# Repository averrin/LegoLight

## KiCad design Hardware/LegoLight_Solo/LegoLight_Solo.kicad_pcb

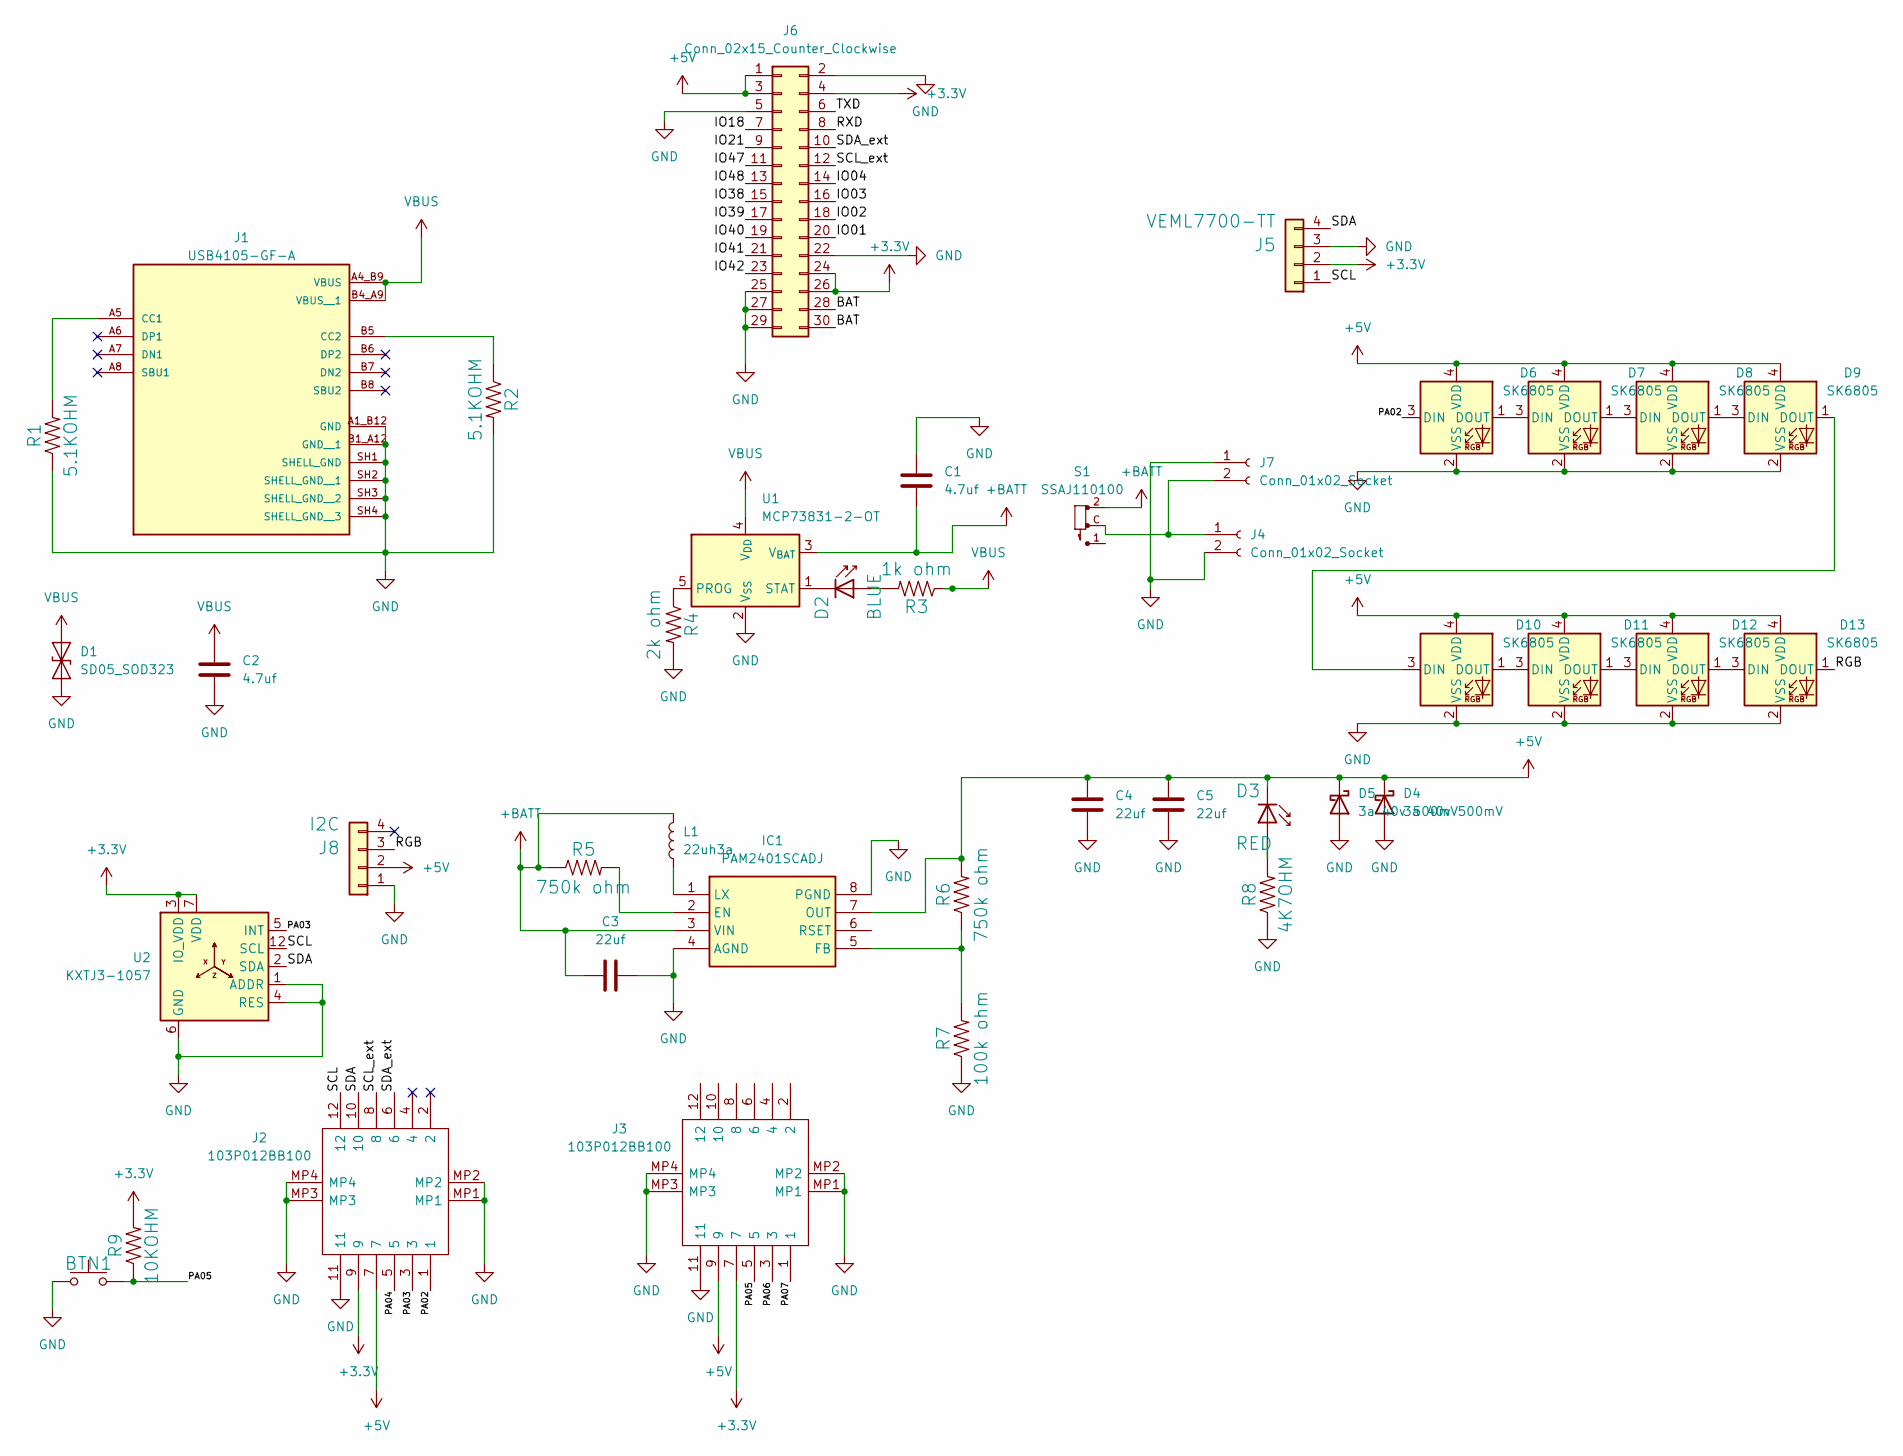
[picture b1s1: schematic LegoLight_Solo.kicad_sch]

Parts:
BTN1: BTN; B3U-1000P; PARTREV C; Mouser Part Number 653-B3U-1000P
C1, C2: 4.7uf; C_0805_2012Metric; Mouser Part Number 80-C0805C475K4RAUTO
C3, C4, C5: 22uf; C_0805_2012Metric; Mouser Part Number 80-C0805C226M9P
D1: SD05_SOD323; D_SOD-323; Mouser Part Number 771-PESD5V0V1771-BA
D2: BLUE; LED_0805_2012Metric_Pad1.15x1.40mm_HandSolder; Mouser Part Number 710-150080BS75000
D3: RED; LED_0805_2012Metric_Pad1.15x1.40mm_HandSolder; Mouser Part Number 696-SML-LXT0805IW
D4, D5: 3a 40v 500mV; D_2010_5025Metric; Mouser Part Number 621-B340A-F
D6, D7, D8, D9, D10, D11, D12, D13: SK6805; LED_SK6812_EC15_1.5x1.5mm; Mouser Part Number 485-4492
IC1: PAM2401SCADJ; SOP65P490X110-8N; Mouser Part Number 621-PAM2401SCADJ
J1: USB4105-GF-A; GCT_USB4105-GF-A; PARTREV B3; Mouser Part Number 640-USB4105-GF-A
J2, J3: 103P012BB100; 103R012BB100; Mouser Part Number 649-103P012BB100
J4: Conn_01x02_Socket; JST_PH_S2B-PH-SM4-TB_1x02-1MP_P2.00mm_Horizontal; Mouser Part Number 485-1769
J5: VEML7700-TT; XDCR_VEML7700-TT; Mouser Part Number 78-VEML7700-TT
J6: Conn_02x15_Counter_Clockwise; PinSocket_2x15_P1.27mm_Vertical; Mouser Part Number M50-3001545
J7: Conn_01x02_Socket; PinHeader_1x02_P2.54mm_Vertical
J8: I2C; SPARKFUN_PRT-14417; Mouser Part Number 474-PRT-14417
L1: 22uh3a; L_Taiyo-Yuden_MD-5050; Mouser Part Number 652-SRP5050FA-220M1
R1, R2: 5.1KOHM; R_0805_2012Metric_Pad1.20x1.40mm_HandSolder; Mouser Part Number 603-RC0805JR-135K1L
R3: 1k ohm; R_0805_2012Metric_Pad1.20x1.40mm_HandSolder; Mouser Part Number CR0805-FX-1601ELF
R4: 2k ohm; R_0805_2012Metric_Pad1.20x1.40mm_HandSolder; Mouser Part Number CR0805-JW-202ELF
R5, R6: 750k ohm; R_0805_2012Metric_Pad1.20x1.40mm_HandSolder; Mouser Part Number 754-RG2012P-754-B-T5
R7: 100k ohm; R_0805_2012Metric_Pad1.20x1.40mm_HandSolder; Mouser Part Number 754-RG2012P-104-B-T5
R8: 4K7OHM; R_0805_2012Metric_Pad1.20x1.40mm_HandSolder; Mouser Part Number 708-RMCF0805FT4K70
R9: 10KOHM; R_0805_2012Metric_Pad1.20x1.40mm_HandSolder; Mouser Part Number 652-CR0805-JW-103ELF
S1: SSAJ110100; SW_SSAJ110100; PARTREV N/A; Mouser Part Number 688-SSAJ110100
U1: MCP73831-2-OT; SOT-23-5; Mouser Part Number 579-MCP73831T-2ACIOT
U2: KXTJ3-1057; KIONIX_KXTJ3-1057; Mouser Part Number 912-KXTJ3-1057

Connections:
+3.3V: J2.9, J3.7, J5.2, J6.4, J6.24, J6.26, R9.2, U2.3 (IO_VDD), U2.7 (VDD), U2.10 (VDD), U2.11 (IO_VDD)
+5V: C4.2, C5.2, D3.1 (K), D4.1 (K), D5.1 (K), D6.4 (VDD), D7.4 (VDD), D8.4 (VDD), D9.4 (VDD), D10.4 (VDD), D11.4 (VDD), D12.4 (VDD), D13.4 (VDD), IC1.7 (OUT), J2.7, J3.9, J6.1, J6.3, J8.2, R6.2
+BATT: C1.2, C3.1, IC1.3 (VIN), L1.2, R5.1, S1.2, U1.3 (V_{BAT})
/BAT: J6.28, J6.30
/IO01: J6.20
/IO02: J6.18
/IO03: J6.16
/IO04: J6.14
/IO18: J6.7
/IO21: J6.9
/IO38: J6.15
/IO39: J6.17
/IO40: J6.19
/IO41: J6.21
/IO42: J6.23
/IO47: J6.11
/IO48: J6.13
/PA02: D6.3 (DIN), J2.1
/PA03: J2.3, U2.5 (INT)
/PA04: J2.5
/PA05: BTN1.2, J3.5, R9.1
/PA06: J3.3
/PA07: J3.1
/RGB: D13.1 (DOUT), J8.3
/RXD: J6.8
/SCL: J2.12, J5.1, U2.12 (SCL)
/SCL_ext: J2.8, J6.12
/SDA: J2.10, J5.4, U2.2 (SDA)
/SDA_ext: J2.6, J6.10
/TXD: J6.6
GND: BTN1.1, C1.1, C2.2, C3.2, C4.1, C5.1, D1.1 (A1), D4.2 (A), D5.2 (A), D6.2 (VSS), D7.2 (VSS), D8.2 (VSS), D9.2 (VSS), D10.2 (VSS), D11.2 (VSS), D12.2 (VSS), D13.2 (VSS), IC1.4 (AGND), IC1.8 (PGND), J1.A1_B12 (GND), J1.B1_A12 (GND__1), J1.SH1 (SHELL_GND), J1.SH2 (SHELL_GND__1), J1.SH3 (SHELL_GND__2), J1.SH4 (SHELL_GND__3), J2.11, J2.MP1, J2.MP2, J2.MP3, J2.MP4, J3.11, J3.MP1, J3.MP2, J3.MP3, J3.MP4, J4.2, J5.3, J6.2, J6.5, J6.22, J6.25, J6.27, J6.29, J7.1, J8.1, R1.1, R2.2, R4.2, R7.1, R8.1, U1.2 (V_{SS}), U2.1 (ADDR), U2.4 (RES), U2.6 (GND), U2.8 (GND), U2.9 (GND)
unnamed: D2.2 (A), R3.2
unnamed: D2.1 (K), U1.1 (STAT)
unnamed: D3.2 (A), R8.2
unnamed: D6.1 (DOUT), D7.3 (DIN)
unnamed: D7.1 (DOUT), D8.3 (DIN)
unnamed: D8.1 (DOUT), D9.3 (DIN)
unnamed: D9.1 (DOUT), D10.3 (DIN)
unnamed: D10.1 (DOUT), D11.3 (DIN)
unnamed: D11.1 (DOUT), D12.3 (DIN)
unnamed: D12.1 (DOUT), D13.3 (DIN)
unnamed: IC1.2 (EN), R5.2
unnamed: IC1.5 (FB), R6.1, R7.2
unnamed: IC1.1 (LX), L1.1
unnamed: J1.A5 (CC1), R1.2
unnamed: J1.B5 (CC2), R2.1
unnamed: J4.1, J7.2, S1.C
unnamed: R4.1, U1.5 (PROG)
VBUS: C2.1, D1.2 (A2), J1.A4_B9 (VBUS), J1.B4_A9 (VBUS__1), R3.1, U1.4 (V_{DD})

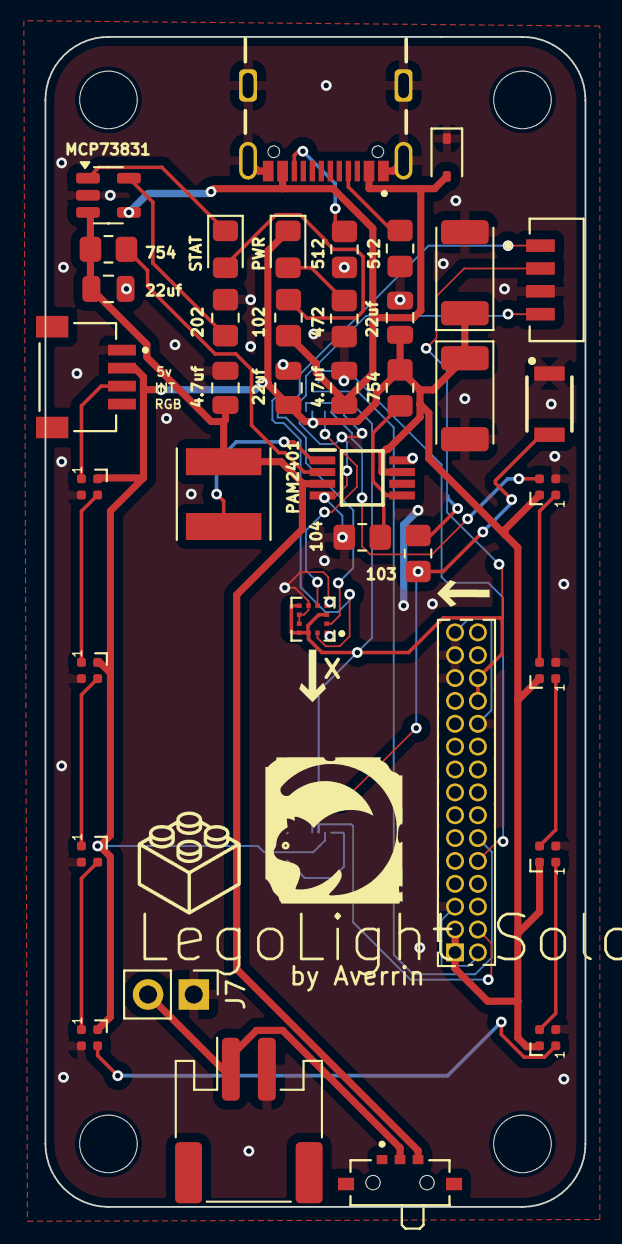
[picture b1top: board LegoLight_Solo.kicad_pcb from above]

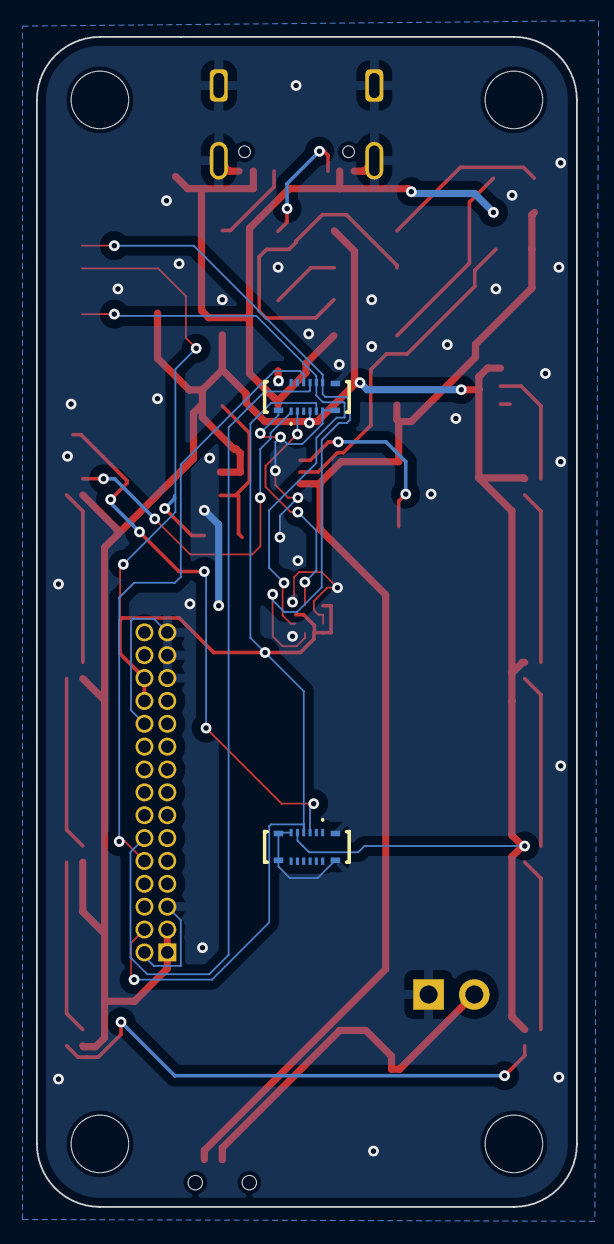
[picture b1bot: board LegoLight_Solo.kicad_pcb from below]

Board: 2 copper layers, 30.0 x 65.0 mm, 45 parts (2 on the bottom side), 31 nets.

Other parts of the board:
H1, H2, H3, H4: MountingHole; MountingHole_3.2mm_M3_DIN965

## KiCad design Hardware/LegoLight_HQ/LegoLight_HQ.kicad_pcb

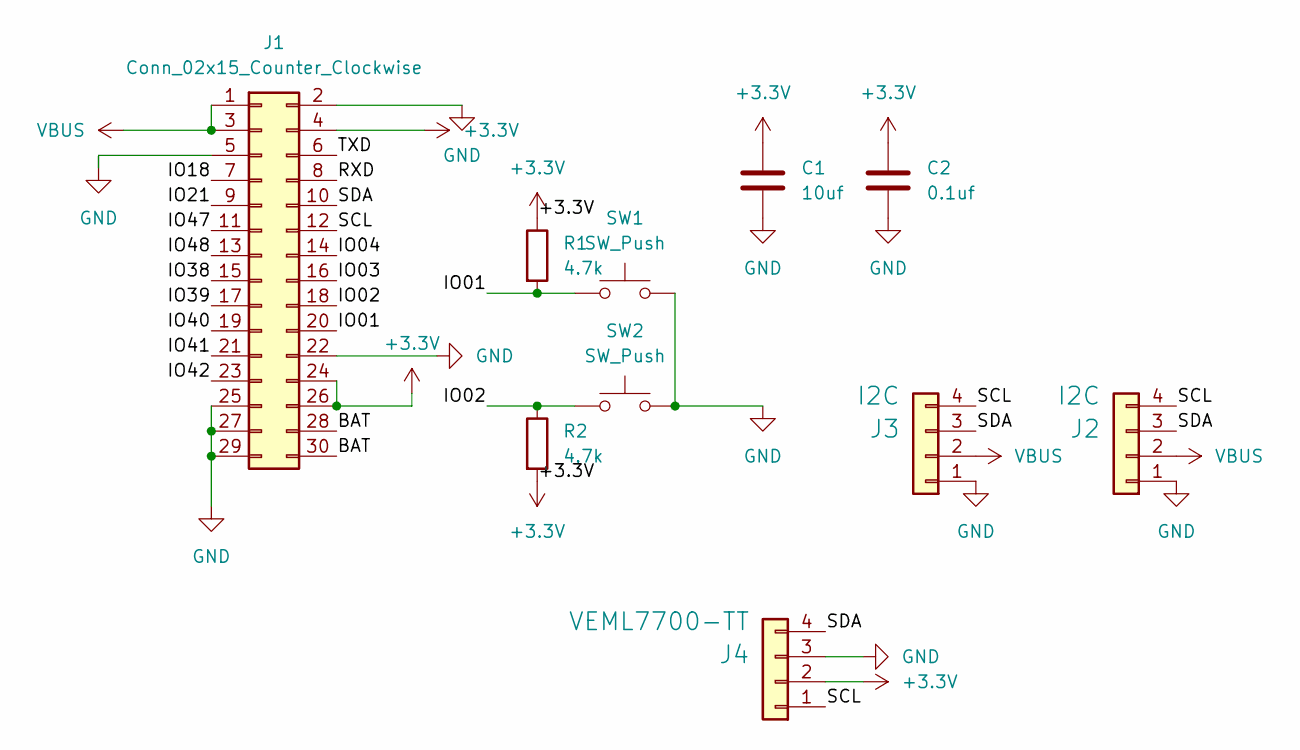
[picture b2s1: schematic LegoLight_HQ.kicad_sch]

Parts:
C1: 10uf; C_0805_2012Metric; Mouser Part Number 80-C0805C106K8R
C2: 0.1uf; C_0805_2012Metric; Mouser Part Number 581-08055C104M4T4A
J1: Conn_02x15_Counter_Clockwise; PinHeader_2x15_P1.27mm_Vertical; Mouser Part Number M50-3001545
J2, J3: I2C; SPARKFUN_PRT-14417; Mouser Part Number 485-4328
J4: VEML7700-TT; XDCR_VEML7700-TT; Mouser Part Number 78-VEML7700-TT
R1, R2: 4.7k; R_1206_3216Metric; Mouser Part Number CR1206-FX-4701ELF
SW1, SW2: SW_Push; SW_MX

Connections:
+3.3V: C1.1, C2.1, J1.4, J1.24, J1.26, J4.2, R1.1, R2.2
/BAT: J1.28, J1.30
/IO01: J1.20, R1.2, SW1.1
/IO02: J1.18, R2.1, SW2.1
/IO03: J1.16
/IO04: J1.14
/IO18: J1.7
/IO21: J1.9
/IO38: J1.15
/IO39: J1.17
/IO40: J1.19
/IO41: J1.21
/IO42: J1.23
/IO47: J1.11
/IO48: J1.13
/RXD: J1.8
/SCL: J1.12, J2.4, J3.4, J4.1
/SDA: J1.10, J2.3, J3.3, J4.4
/TXD: J1.6
GND: C1.2, C2.2, J1.2, J1.5, J1.22, J1.25, J1.27, J1.29, J2.1, J3.1, J4.3, SW1.2, SW2.2
VBUS: J1.1, J1.3, J2.2, J3.2

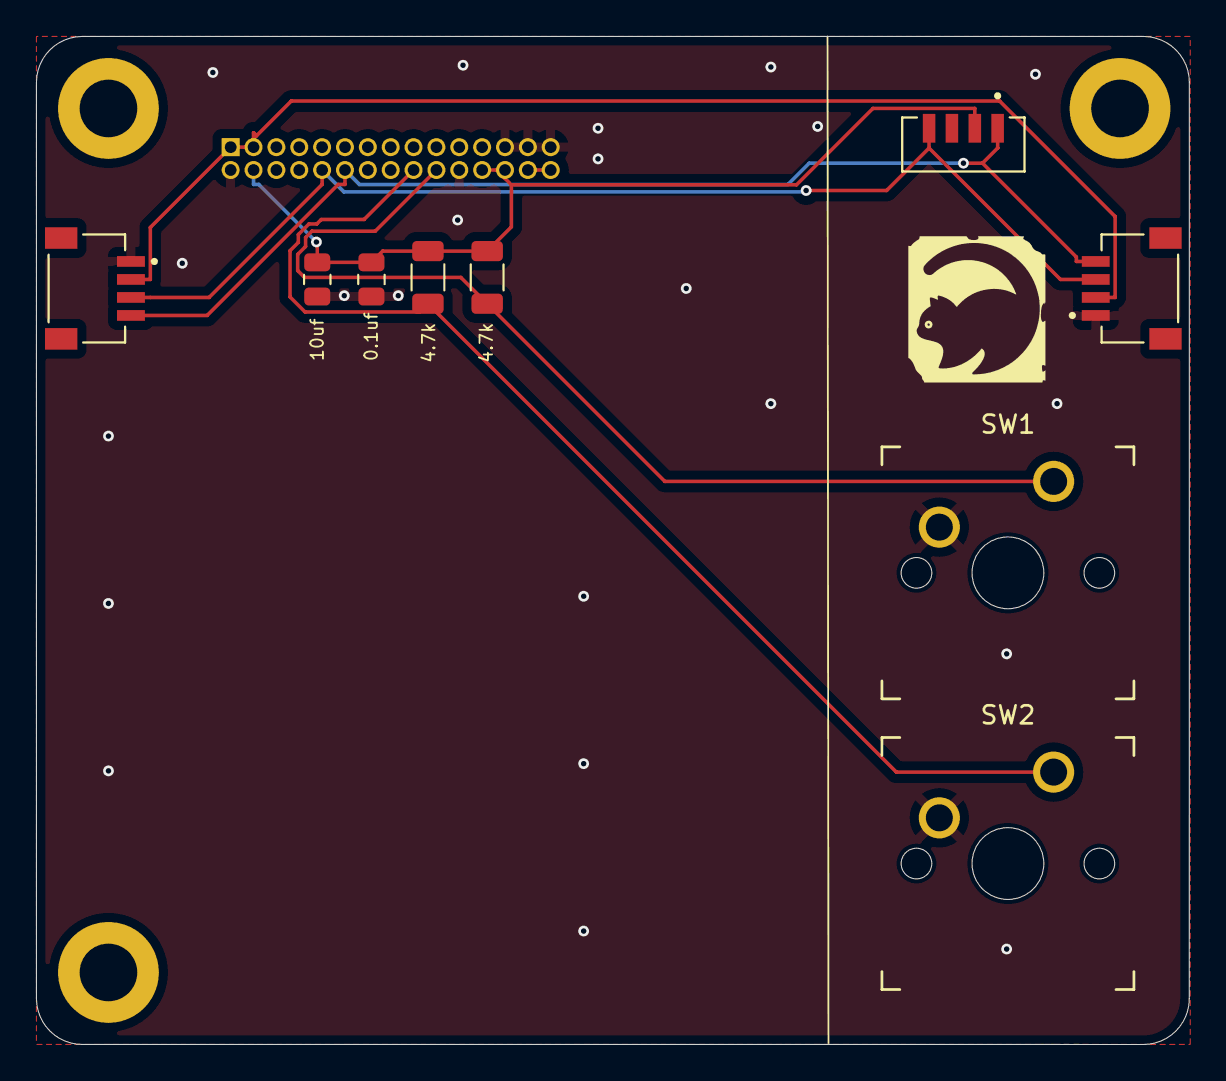
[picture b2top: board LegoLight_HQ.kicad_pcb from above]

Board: 2 copper layers, 64.1 x 56.0 mm, 13 parts (1 on the bottom side), 8 nets.

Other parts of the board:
REF1, REF2, REF3: MountingHole_3.2mm_M3_DIN965_Pad

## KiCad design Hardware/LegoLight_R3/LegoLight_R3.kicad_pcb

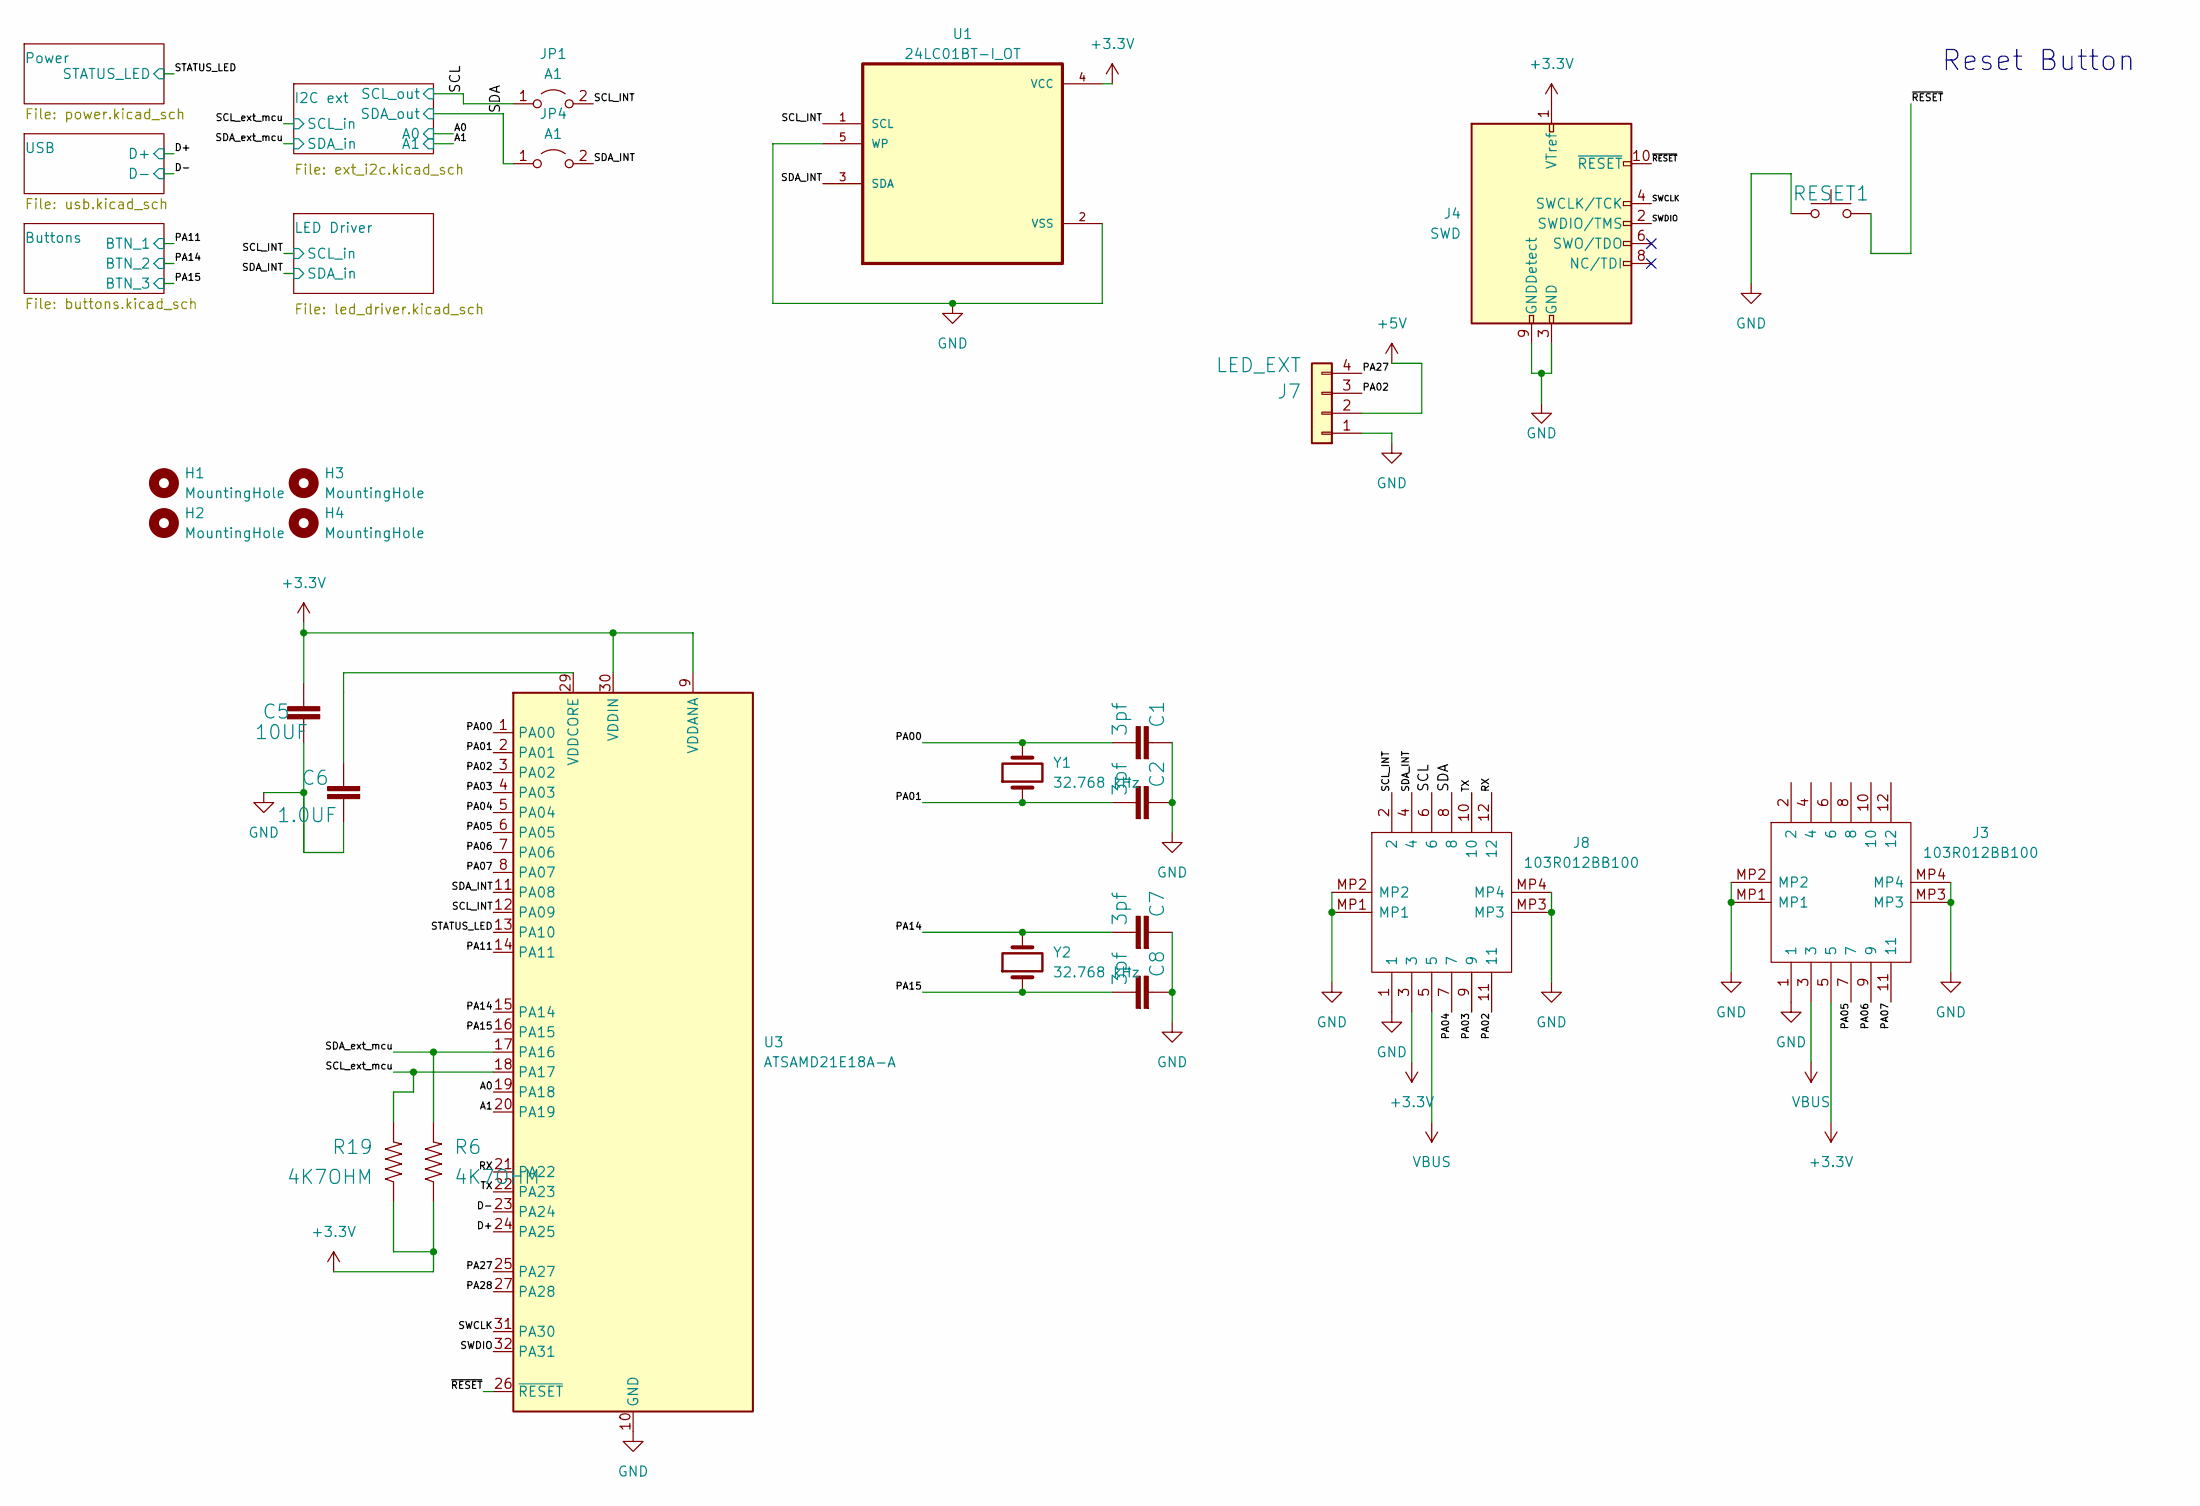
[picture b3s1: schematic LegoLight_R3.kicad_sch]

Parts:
C1, C2, C7, C8: 3pf; C_0805_2012Metric; Mouser Part Number 187-CL21B105KAFNNNE
C5: 10UF; C_0805_2012Metric_Pad1.18x1.45mm_HandSolder; Mouser Part Number 187-CL21A106KOQNNNG
C6: 1.0UF; C_0805_2012Metric_Pad1.18x1.45mm_HandSolder; Mouser Part Number 187-CL21B105KAFNNNE
H1, H2, H3, H4: MountingHole; MountingHole_3.2mm_M3_DIN965
J3, J8: 103R012BB100; Mouser Part Number 649-103R012BB100
J4: SWD; PinSocket_2x05_P1.27mm_Vertical
J7: LED_EXT; SPARKFUN_PRT-14417; Mouser Part Number 485-4328
JP1, JP4: A1; SolderJumper-2_P1.3mm_Open_RoundedPad1.0x1.5mm
R6, R19: 4K7OHM; R_0805_2012Metric_Pad1.20x1.40mm_HandSolder; Mouser Part Number 708-RMCF0805FT4K70
RESET1: TL3305AF160QG; B3U-1000P; PARTREV C; Mouser Part Number 653-B3U-1000P
U1: 24LC01BT-I_OT; SOT-353_SC-70-5; Mouser Part Number 579-24LC01BT-I/OT
U3: ATSAMD21E18A-A; QFN-32-1EP_5x5mm_P0.5mm_EP3.3x3.3mm; Mouser Part Number 556-ATSAMD21E18A-MUT
Y1, Y2: 32.768 kHz; Crystal_SMD_MicroCrystal_CC8V-T1A-2Pin_2.0x1.2mm; Mouser Part Number 815-ABS06-32.768K-T

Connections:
+3.3V: C5.1, J3.5, J4.1 (VTref), J8.3, R6.1, R19.1, U1.4 (VCC), U3.9 (VDDANA), U3.30 (VDDIN); also elsewhere on the board
+5V: J7.2; also elsewhere on the board
/A0: U3.19 (PA18); also elsewhere on the board
/A1: U3.20 (PA19); also elsewhere on the board
/D+: U3.24 (PA25); also elsewhere on the board
/D-: U3.23 (PA24); also elsewhere on the board
/PA00: C1.1, U3.1 (PA00), Y1.2
/PA01: C2.1, U3.2 (PA01), Y1.1
/PA02: J7.3, J8.11, U3.3 (PA02)
/PA03: J8.9, U3.4 (PA03)
/PA04: J8.7, U3.5 (PA04)
/PA05: J3.7, U3.6 (PA05)
/PA06: J3.9, U3.7 (PA06)
/PA07: J3.11, U3.8 (PA07)
/PA11: U3.14 (PA11); also elsewhere on the board
/PA14: C7.1, U3.15 (PA14), Y2.2
/PA15: C8.1, U3.16 (PA15), Y2.1
/PA27: J7.4, U3.25 (PA27)
/PA28: U3.27 (PA28)
/RX: J8.12, U3.21 (PA22)
/SCL: J8.6, JP1.1 (A); also elsewhere on the board
/SCL_INT: J8.2, JP1.2 (B), U1.1 (SCL), U3.12 (PA09); also elsewhere on the board
/SCL_ext_mcu: R19.2, U3.18 (PA17); also elsewhere on the board
/SDA: J8.8, JP4.1 (A); also elsewhere on the board
/SDA_INT: J8.4, JP4.2 (B), U1.3 (SDA), U3.11 (PA08); also elsewhere on the board
/SDA_ext_mcu: R6.2, U3.17 (PA16); also elsewhere on the board
/STATUS_LED: U3.13 (PA10); also elsewhere on the board
/SWCLK: J4.4 (SWCLK/TCK), U3.31 (PA30)
/SWDIO: J4.2 (SWDIO/TMS), U3.32 (PA31)
/TX: J8.10, U3.22 (PA23)
/~RESET: J4.10 (~RESET), RESET1.2, U3.26 (~RESET)
GND: C1.2, C2.2, C5.2, C6.1, C7.2, C8.2, J3.1, J3.MP1, J3.MP2, J3.MP3, J3.MP4, J4.3 (GND), J4.5 (GND), J4.9 (GNDDetect), J7.1, J8.1, J8.MP1, J8.MP2, J8.MP3, J8.MP4, RESET1.1, U1.2 (VSS), U1.5 (WP), U3.10 (GND), U3.28 (GND); also elsewhere on the board
unnamed: C6.2, U3.29 (VDDCORE)
VBUS: J3.3, J8.5; also elsewhere on the board

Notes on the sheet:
Reset Button

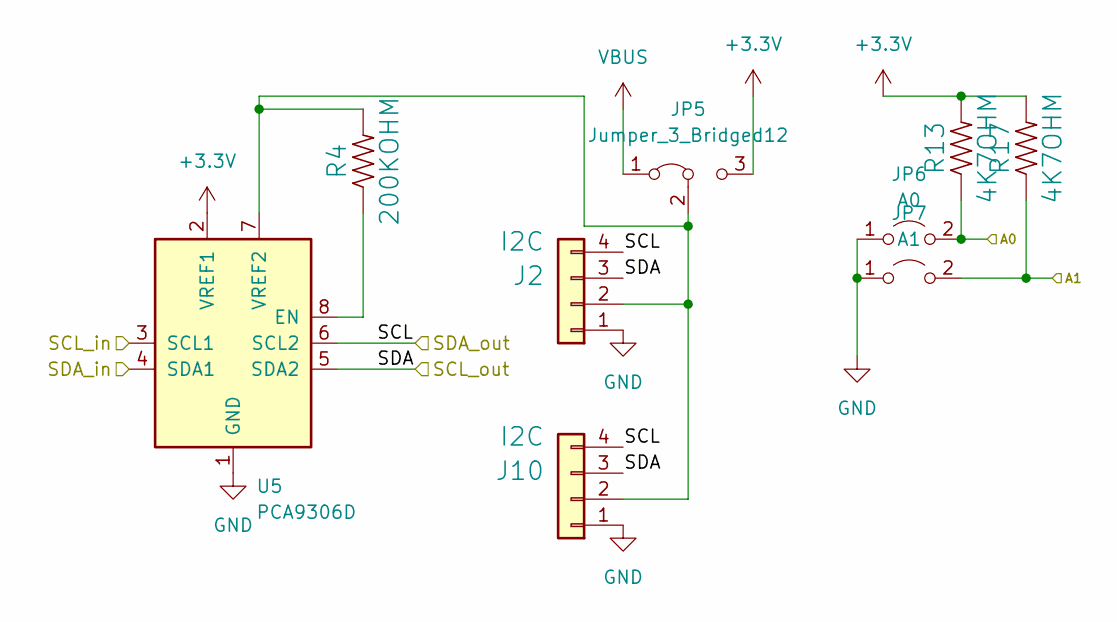
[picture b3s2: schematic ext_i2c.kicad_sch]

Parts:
J2, J10: I2C; SPARKFUN_PRT-14417; Mouser Part Number 485-4328
JP5: Jumper_3_Bridged12; SolderJumper-3_P1.3mm_Bridged12_RoundedPad1.0x1.5mm
JP6: A0; SolderJumper-2_P1.3mm_Open_RoundedPad1.0x1.5mm
JP7: A1; SolderJumper-2_P1.3mm_Open_RoundedPad1.0x1.5mm
R4: 200KOHM; R_0805_2012Metric_Pad1.20x1.40mm_HandSolder; Mouser Part Number 652-CR0805FX-2003ELF
R13, R17: 4K7OHM; R_0805_2012Metric_Pad1.20x1.40mm_HandSolder; Mouser Part Number 708-RMCF0805FT4K70
U5: PCA9306D; TSSOP-8_4.4x3mm_P0.65mm; Mouser Part Number 771-PCA9306DP-T

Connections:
+3.3V: JP5.3 (B), R13.2, R17.2, U5.2 (VREF1); also elsewhere on the board
/A0: JP6.2 (B), R13.1; also elsewhere on the board
/A1: JP7.2 (B), R17.1; also elsewhere on the board
/SCL: J2.3, J10.3, U5.5 (SDA2); also elsewhere on the board
/SCL_ext_mcu: U5.3 (SCL1); also elsewhere on the board
/SDA: J2.4, J10.4, U5.6 (SCL2); also elsewhere on the board
/SDA_ext_mcu: U5.4 (SDA1); also elsewhere on the board
GND: J2.1, J10.1, JP6.1 (A), JP7.1 (A), U5.1 (GND); also elsewhere on the board
unnamed: J2.2, J10.2, JP5.2 (C), R4.2, U5.7 (VREF2)
unnamed: R4.1, U5.8 (EN)
VBUS: JP5.1 (A); also elsewhere on the board

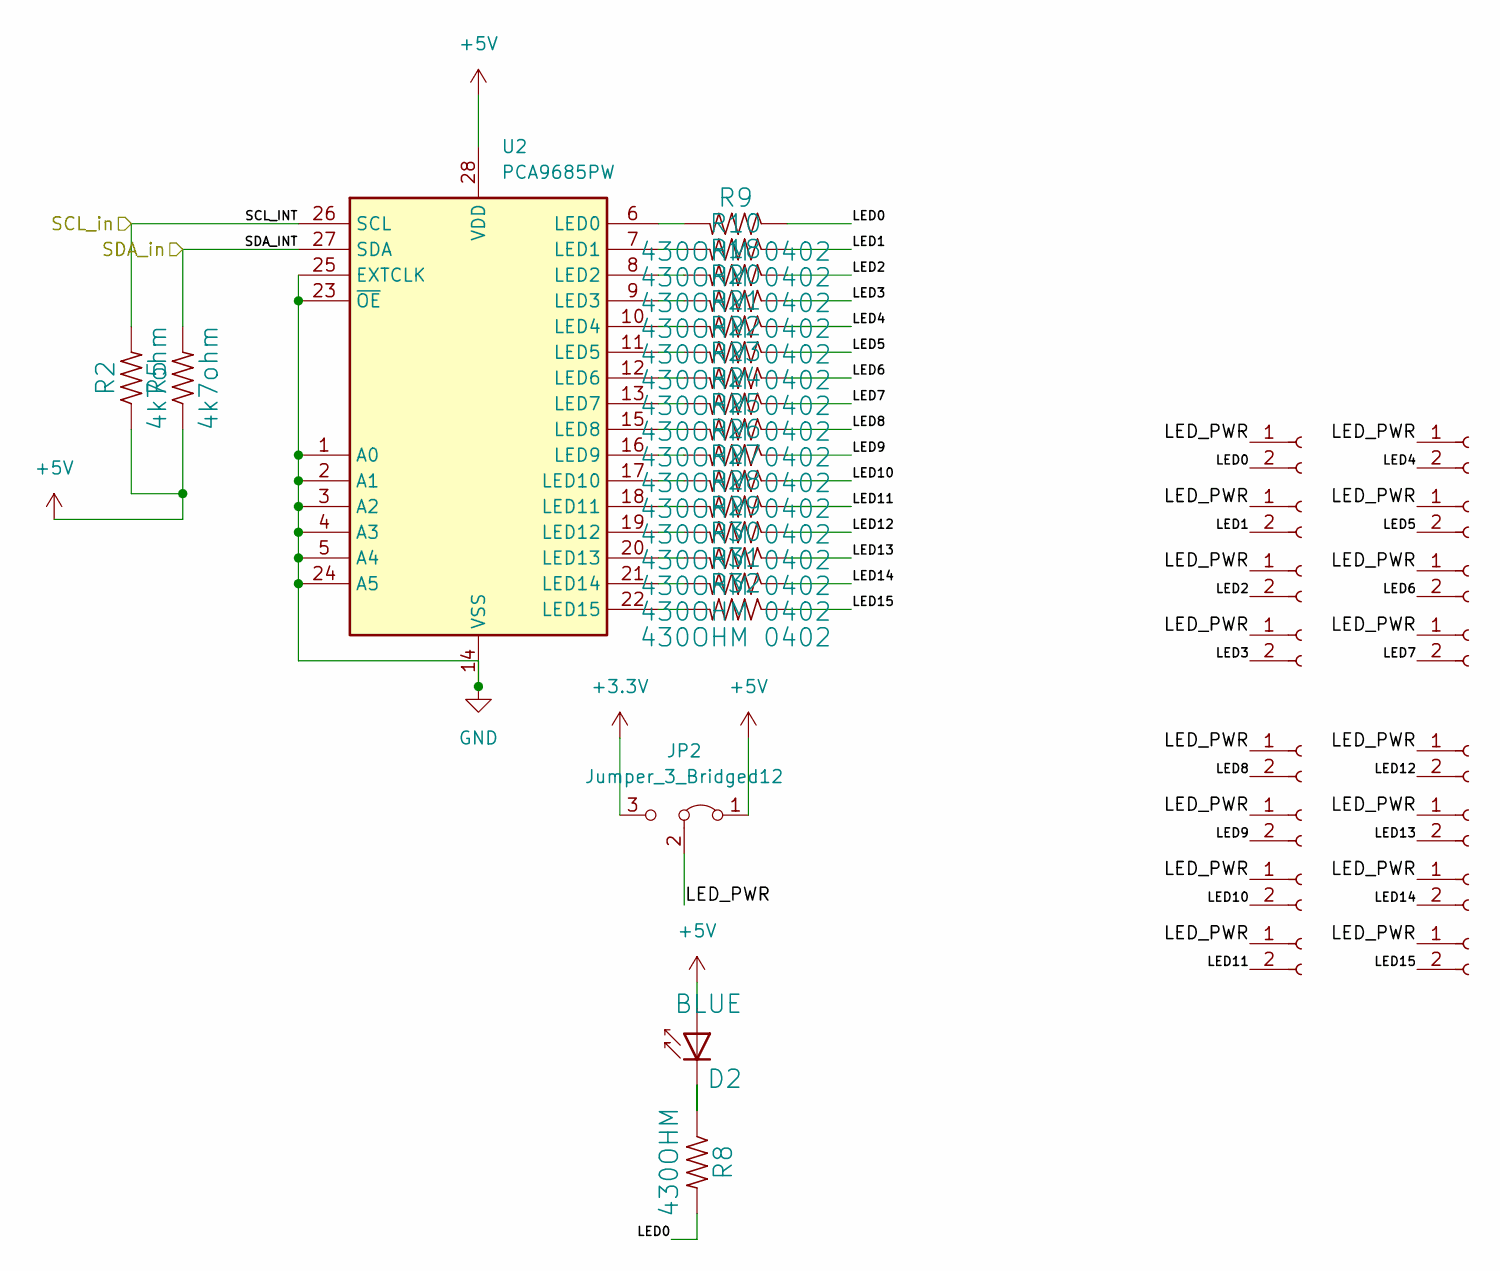
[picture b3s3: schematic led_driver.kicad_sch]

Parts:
D2: BLUE; LED_0805_2012Metric_Pad1.15x1.40mm_HandSolder; Mouser Part Number 710-150080BS75000
J11, J12, J13, J14, J15, J16, J17, J18, J19, J20, J21, J22, J23, J24, J25, J26: Conn_01x02_Socket; jst_gh_2p_1.25
JP2: Jumper_3_Bridged12; SolderJumper-3_P1.3mm_Bridged12_RoundedPad1.0x1.5mm
R2, R5: 4k7ohm; R_0805_2012Metric_Pad1.20x1.40mm_HandSolder; Mouser Part Number 708-RMCF0805FT4K70
R8: 430OHM; R_0805_2012Metric_Pad1.20x1.40mm_HandSolder; Mouser Part Number 652-CR0805JW-431ELF
R9, R10, R18, R20, R21, R22, R23, R24, R25, R26, R27, R28, R29, R30, R31, R32: 430OHM 0402; R_0402_1005Metric_Pad0.72x0.64mm_HandSolder; Mouser Part Number 603-RC0402JR-07430RL
U2: PCA9685PW; TSSOP-28_4.4x9.7mm_P0.65mm; Mouser Part Number 771-PCA9685PW,112

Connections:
+3.3V: JP2.3 (B); also elsewhere on the board
+5V: D2.2 (A), JP2.1 (A), R2.1, R5.1, U2.28 (VDD); also elsewhere on the board
/LED Driver/LED0: J11.2, R8.2, R9.1
/LED Driver/LED1: J12.2, R10.1
/LED Driver/LED2: J13.2, R18.1
/LED Driver/LED3: J14.2, R20.1
/LED Driver/LED4: J15.2, R21.1
/LED Driver/LED5: J16.2, R22.1
/LED Driver/LED6: J17.2, R23.1
/LED Driver/LED7: J18.2, R24.1
/LED Driver/LED8: J19.2, R25.1
/LED Driver/LED9: J20.2, R26.1
/LED Driver/LED10: J21.2, R27.1
/LED Driver/LED11: J22.2, R28.1
/LED Driver/LED12: J23.2, R29.1
/LED Driver/LED13: J24.2, R30.1
/LED Driver/LED14: J25.2, R31.1
/LED Driver/LED15: J26.2, R32.1
/LED Driver/LED_PWR: J11.1, J12.1, J13.1, J14.1, J15.1, J16.1, J17.1, J18.1, J19.1, J20.1, J21.1, J22.1, J23.1, J24.1, J25.1, J26.1, JP2.2 (C)
/SCL_INT: R2.2, U2.26 (SCL); also elsewhere on the board
/SDA_INT: R5.2, U2.27 (SDA); also elsewhere on the board
GND: U2.1 (A0), U2.2 (A1), U2.3 (A2), U2.4 (A3), U2.5 (A4), U2.14 (VSS), U2.23 (~OE), U2.24 (A5), U2.25 (EXTCLK); also elsewhere on the board
unnamed: D2.1 (K), R8.1
unnamed: R9.2, U2.6 (LED0)
unnamed: R10.2, U2.7 (LED1)
unnamed: R18.2, U2.8 (LED2)
unnamed: R20.2, U2.9 (LED3)
unnamed: R21.2, U2.10 (LED4)
unnamed: R22.2, U2.11 (LED5)
unnamed: R23.2, U2.12 (LED6)
unnamed: R24.2, U2.13 (LED7)
unnamed: R25.2, U2.15 (LED8)
unnamed: R26.2, U2.16 (LED9)
unnamed: R27.2, U2.17 (LED10)
unnamed: R28.2, U2.18 (LED11)
unnamed: R29.2, U2.19 (LED12)
unnamed: R30.2, U2.20 (LED13)
unnamed: R31.2, U2.21 (LED14)
unnamed: R32.2, U2.22 (LED15)

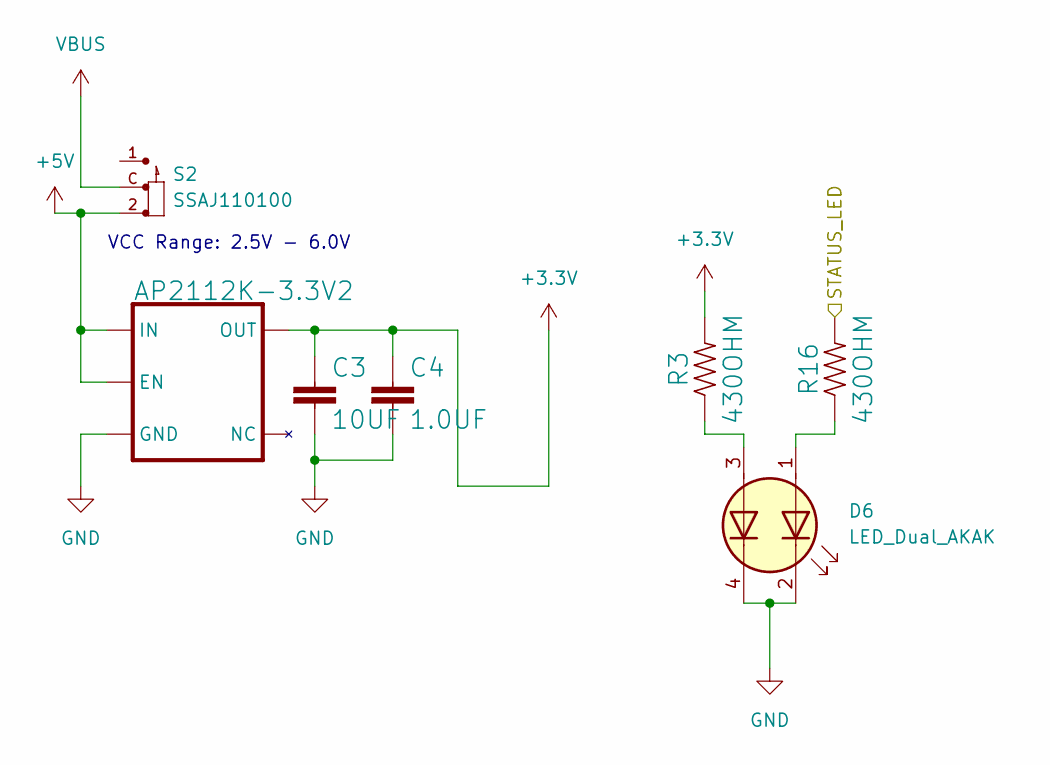
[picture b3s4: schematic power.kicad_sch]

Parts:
AP2112K-3.3V2: AP2112K-3.3V; SOT-23-5_HandSoldering; Mouser Part Number 621-AP2112K-3.3TRG1
C3: 10UF; C_0805_2012Metric_Pad1.18x1.45mm_HandSolder; Mouser Part Number 187-CL21A106KOQNNNG
C4: 1.0UF; C_0805_2012Metric_Pad1.18x1.45mm_HandSolder; Mouser Part Number 187-CL21B105KAFNNNE
D6: LED_Dual_AKAK; LED_APHB1608LZGKSURKC; Mouser Part Number 604-APHB1608LZGKSURK
R3, R16: 430OHM; R_0402_1005Metric_Pad0.72x0.64mm_HandSolder; Mouser Part Number 652-CR0805JW-431ELF
S2: SSAJ110100; SW_SSAJ110100; PARTREV N/A; Mouser Part Number 688-SSAJ110100

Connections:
+3.3V: AP2112K-3.3V2.5 (OUT), C3.1, C4.1, R3.2; also elsewhere on the board
+5V: AP2112K-3.3V2.1 (IN), AP2112K-3.3V2.3 (EN), S2.2; also elsewhere on the board
/STATUS_LED: R16.2; also elsewhere on the board
GND: AP2112K-3.3V2.2 (GND), C3.2, C4.2, D6.2 (K1), D6.4 (K2); also elsewhere on the board
unnamed: D6.1 (A1), R16.1
unnamed: D6.3 (A2), R3.1
VBUS: S2.C; also elsewhere on the board

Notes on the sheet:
VCC Range: 2.5V - 6.0V

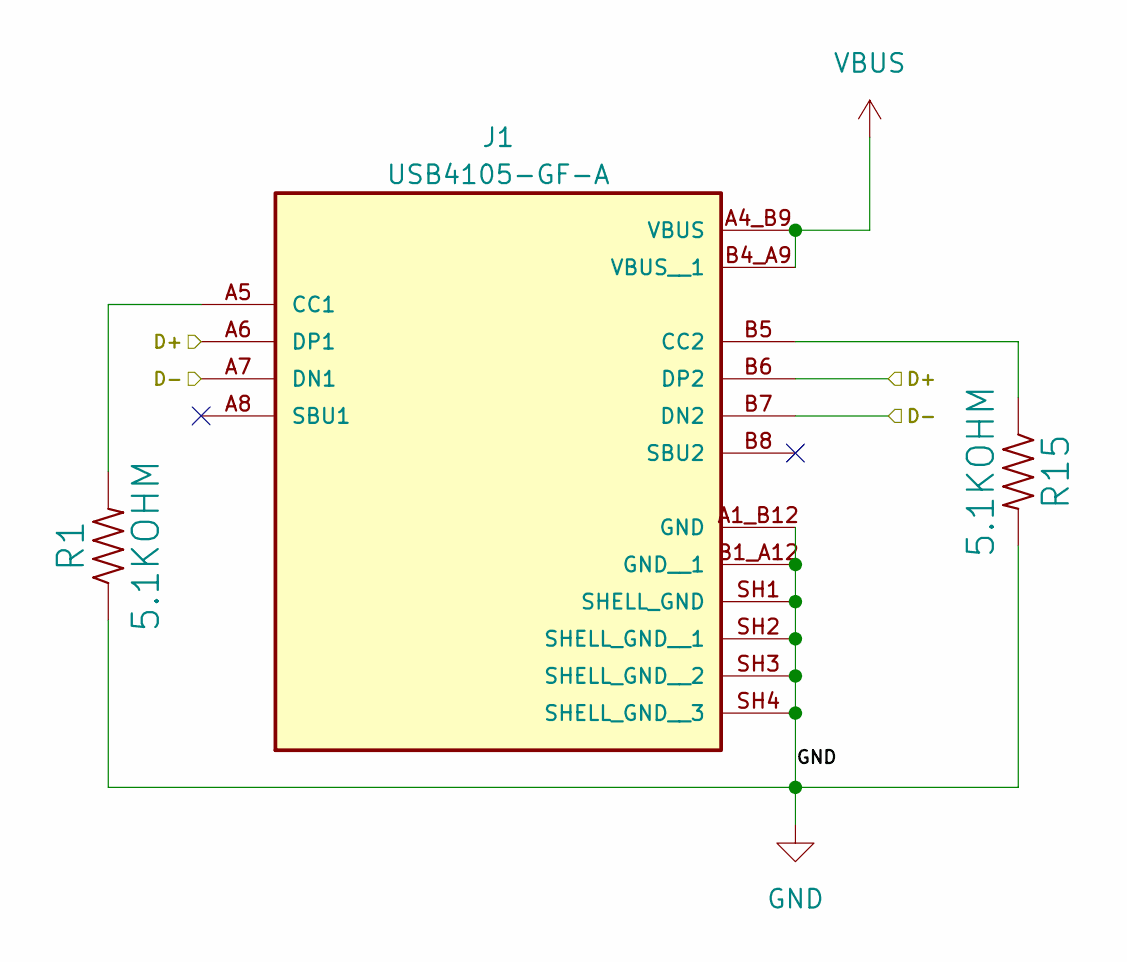
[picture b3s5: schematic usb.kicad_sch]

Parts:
J1: USB4105-GF-A; GCT_USB4105-GF-A; PARTREV B3; Mouser Part Number 640-USB4105-GF-A
R1, R15: 5.1KOHM; R_0805_2012Metric_Pad1.20x1.40mm_HandSolder; Mouser Part Number 603-RC0805JR-135K1L

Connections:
/D+: J1.A6 (DP1), J1.B6 (DP2); also elsewhere on the board
/D-: J1.A7 (DN1), J1.B7 (DN2); also elsewhere on the board
GND: J1.A1_B12 (GND), J1.B1_A12 (GND__1), J1.SH1 (SHELL_GND), J1.SH2 (SHELL_GND__1), J1.SH3 (SHELL_GND__2), J1.SH4 (SHELL_GND__3), R1.1, R15.2; also elsewhere on the board
unnamed: J1.A5 (CC1), R1.2
unnamed: J1.B5 (CC2), R15.1
VBUS: J1.A4_B9 (VBUS), J1.B4_A9 (VBUS__1); also elsewhere on the board
